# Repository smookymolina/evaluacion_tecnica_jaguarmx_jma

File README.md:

# Sistema de Extracción de Aire Caliente para Gabinete de Telecomunicaciones
## Jaguar de México — Evaluación Técnica
**Candidato:** Ing. Jair Molina Arce  
**Fecha:** 30 de junio de 2026

---

## Descripción del Proyecto
Este proyecto consiste en el diseño físico y lógico (hardware y firmware) de un sistema de control automático para la extracción de aire caliente en un gabinete de telecomunicaciones. El sistema compara la temperatura interna (`TEMP_INT`) con la temperatura externa (`TEMP_EXT`) y gestiona de forma dinámica:
1. **Compuertas mecánicas:** Operadas por un actuador lineal DFRobot FIT0803 a través de un puente H Toshiba TB6612FNG.
2. **Extractor/Ventilador:** Ventilador industrial Mechatronics MR1238E48B-FSR (48V DC) controlado por modulación low-side con un MOSFET de potencia IRL520N.

El núcleo de control está basado en el microcontrolador **Seeed Studio XIAO RP2350**, programado en MicroPython con una arquitectura de Máquina de Estados Finitos (FSM) y supervisado por un watchdog timer por hardware (WDT).

---

## Estructura del Repositorio

- `firmware/`: Código fuente de control en MicroPython.
  - `main.py`: Punto de entrada, inicialización y gestión de fallos.
  - `fsm.py`: Implementación de la FSM (INIT, READING, COOLING, IDLE, ERROR).
  - `adc_ntc.py`: Adquisición analógica con promedio móvil (trimmed mean, N=8) y conversión Beta.
  - `dip_switch.py`: Configuración de setpoint de histéresis mediante DIP switch.
  - `hbridge.py`: Control de dirección y habilitación del actuador con alimentación segura al WDT.
  - `fan.py`: Módulo de conmutación del MOSFET del ventilador.
- `kicad/`: Archivos del diseño de hardware en KiCad v8/v9.
  - `PCB/PCB.kicad_pro`: Archivo de proyecto de KiCad.
  - `PCB/PCB.kicad_sch`: Esquemático del circuito (Componentes colocados, especificaciones y BOM al 100%).
  - `PCB/PCB.kicad_pcb`: Diseño físico del PCB.
  - `PCB/sym-lib-table`: Tabla de mapeo de librerías de símbolos.
- `datasheets/`: Especificaciones técnicas en markdown y PDFs de los componentes clave.
- `FASE2.1_Netlist_Corregido_JaguarMX.md`: Netlist blindado de interconexiones (verdad de referencia).
- `FASE3_Guia_Esquematico_KiCad_JaguarMX.md`: Guía de diseño del esquemático.
- `FASE4_Layout_PCB_KiCad_JaguarMX.md`: Guía para el trazado de PCB y distribución de componentes.
- `ETISEJr_JairMolina.md`: Respuestas de evaluación y bitácora de uso de IA.
- `EvaluacionTecnica_SistemasEmbebidosJr_JaguarDeMexico.pdf`: Documento de requerimientos oficiales.
- `Cronograma_EvaluacionTecnica_JairMolina.docx`: Planificación de las fases del examen.
- `parse_sch.py`: Script para extraer la BOM directamente del esquemático KiCad.
- `test_firmware.py` / `micropython.py` / `mock_*.py`: Entorno local de pruebas unitarias y mocks de hardware.
- `package_project.ps1`: Script automatizado para el empaquetado del entregable final.

---

## Modificaciones de Hardware Incorporadas (Fase 2.1)
- **[MOD-1] Remapeo de SW2:** Movido de GP7 (back pad inaccesible) a GP8 (castellación lateral del Seeed XIAO RP2350).
- **[MOD-2] Clamping de ADC:** Reemplazo de diodos TVS SMBJ3.3A por diodos Schottky duales BAT54S en configuración de clamp activo post-filtro.
- **[MOD-3] Inmunidad EMI en DIP Switch:** Pull-ups externas de 10kΩ y condensadores de bypass de 100nF en cada canal.
- **[MOD-4] Selector J9:** Reemplazo del puente de soldadura por un header de 3 pines para seleccionar control del Gate directo o con driver TC4420.
- **[MOD-5] Star Ground:** Unión única AGND-PGND mediante Net-Tie de cobre directo (0Ω), eliminando la ferrita.
- **[Desacoplo de U4 (Nuevo)] Capacitor C15:** Adición del capacitor de desacoplo `C15` (100nF, DNP por defecto) para alimentar adecuadamente al driver TC4420 si se decide poblar en Configuración Activa-B.
- **[Conexión GND U4 (Nuevo)] Corrección de Plano:** Enrutamiento de la tierra de U4 (GND, pines 1, 2, 4) al plano de potencia `PGND` (en lugar del plano analógico `AGND`) para evitar la inyección de ruidos transitorios de 6A pico en el plano sensible de lectura.
- **[Consolidación (Nuevo)] Remoción de Excesos:** Eliminación de la resistencia fantasma redundante `R8` del diseño del circuito.

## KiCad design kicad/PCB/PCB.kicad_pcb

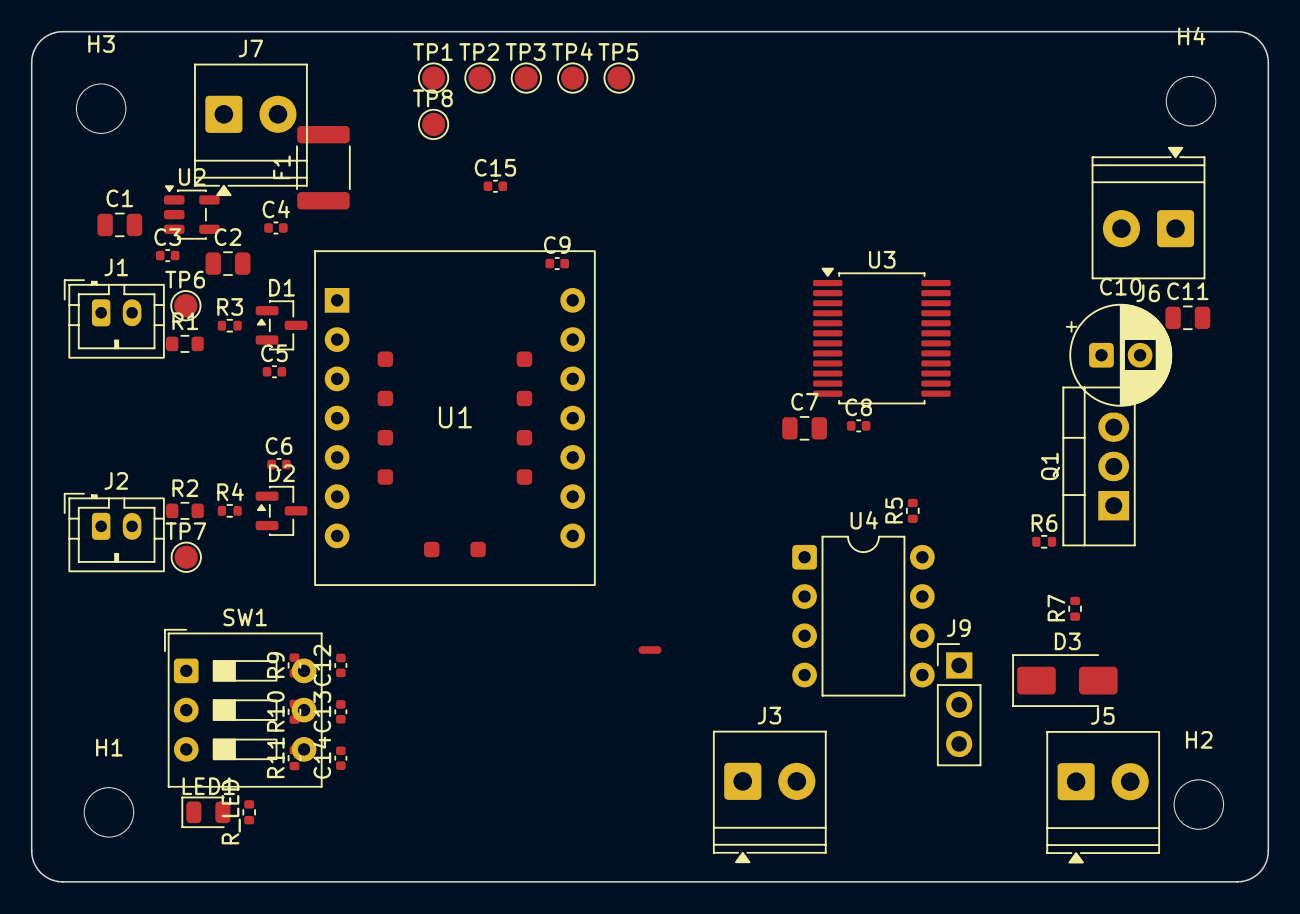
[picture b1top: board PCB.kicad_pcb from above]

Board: 2 copper layers, 80.0 x 55.0 mm, 57 parts (0 on the bottom side), 25 nets, no tracks yet.

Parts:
C1, C2: 10uF; C_0805_2012Metric
C3, C4, C5, C6, C8, C9, C12, C13, C14, C15: 0.1uF; C_0402_1005Metric
C7: 47uF; C_0805_2012Metric
C10: 100uF/63V; CP_Radial_D6.3mm_P2.50mm
C11: 100nF/63V; C_0805_2012Metric
D1, D2: BAT54S; SOT-23
D3: US1M; D_SMA
F1: 500mA; Fuse_1812_4532Metric
H1, H2, H3, H4: MountingHole_3.2mm_M3
J1, J2: JST_2mm; JST_PH_B2B-PH-K_1x02_P2.00mm_Vertical
J3, J5, J6, J7: 3.5mm; TerminalBlock_Phoenix_PT-1,5-2-3.5-H_1x02_P3.50mm_Horizontal
J9: Selector_TC4420; PinHeader_1x03_P2.54mm_Vertical
LED1: LED_Green; LED_0805_2012Metric
NT1: NetTie_2; NetTie-2_SMD_Pad0.5mm
Q1: IRL520N; TO-220-3_Vertical
R1, R2: 10k 0.1%; R_0603_1608Metric
R3, R4: 1k; R_0402_1005Metric
R5, R7, R9, R10, R11: 10k; R_0402_1005Metric
R6: 330R; R_0402_1005Metric
R_LED: 1k; R_0402_1005Metric
SW1: SW_DIP_x03; SW_DIP_SPSTx03_Slide_9.78x9.8mm_W7.62mm_P2.54mm
TP1, TP2, TP3, TP4, TP5, TP6, TP7, TP8: 1.25mm; TestPoint_Pad_D1.5mm
U1: XIAO-RP2350-DIP
U2: AP2112K-3.3; SOT-23-5
U3: TB6612FNG; SSOP-24_5.3x8.2mm_P0.65mm
U4: TC4420; DIP-8_W7.62mm

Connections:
/+3V3: C9.2, D1.2, D2.2, F1.2, R1.1, R2.2, R5.1, R9.2, R10.2, R11.2, R_LED.1, TP1.1, U1.12, U3.20
/+5V: C1.1, C3.2, C7.1, C8.1, C15.1, J7.1, TP2.1, U2.1, U2.3, U3.13, U3.14, U3.24, U4.5, U4.7, U4.8
/+48V: C10.1, C11.1, D3.1, J5.1, J6.1, TP3.1
/AGND: C1.2, C2.2, C3.1, C4.2, C5.1, C6.2, C9.1, C12.2, C13.2, C14.2, D1.1, D2.1, J1.2, J2.1, LED1.1, NT1.1, SW1.2, SW1.4, SW1.6, TP5.1, U1.13, U1.24, U2.2, U3.15, U3.16, U3.17, U3.18
/NET_3V3_LDO: C2.1, C4.1, F1.1, U2.5
/NET_AIN1: U1.9, U3.21
/NET_AIN2: U1.8, U3.22
/NET_AO1: J3.1, U3.1, U3.2
/NET_AO2: J3.2, U3.5, U3.6
/NET_FAN_HS: D3.2, J6.2, Q1.2
/NET_LED_ANODE: LED1.2, R_LED.2
/NET_MOTOR_EN: U1.11, U3.23
/NET_Q1_GATE: Q1.1, R6.2, R7.2, TP8.1
/NET_STBY: R5.2, U3.19
/NET_SW1: C12.1, R9.1, SW1.1, U1.5
/NET_SW2: C13.1, R10.1, SW1.5, U1.6
/NET_SW3: C14.1, R11.1, SW1.3, U1.7
/NET_TEMP_EXT_DIV: J2.2, R2.1, R4.1
/NET_TEMP_EXT_FILT: C6.1, D2.3, R4.2, TP7.1, U1.2
/NET_TEMP_INT_DIV: J1.1, R1.2, R3.1
/NET_TEMP_INT_FILT: C5.2, D1.3, R3.2, TP6.1, U1.1
/NET_VENT: J9.1, U1.10, U4.3
/NET_VENT_DRV: J9.3, U4.6
/NET_VENT_GATE: J9.2, R6.1
/PGND: C7.2, C8.2, C10.2, C11.2, C15.2, J5.2, J7.2, NT1.2, Q1.3, R7.1, TP4.1, U3.3, U3.4, U3.9, U3.10, U4.1, U4.2, U4.4
